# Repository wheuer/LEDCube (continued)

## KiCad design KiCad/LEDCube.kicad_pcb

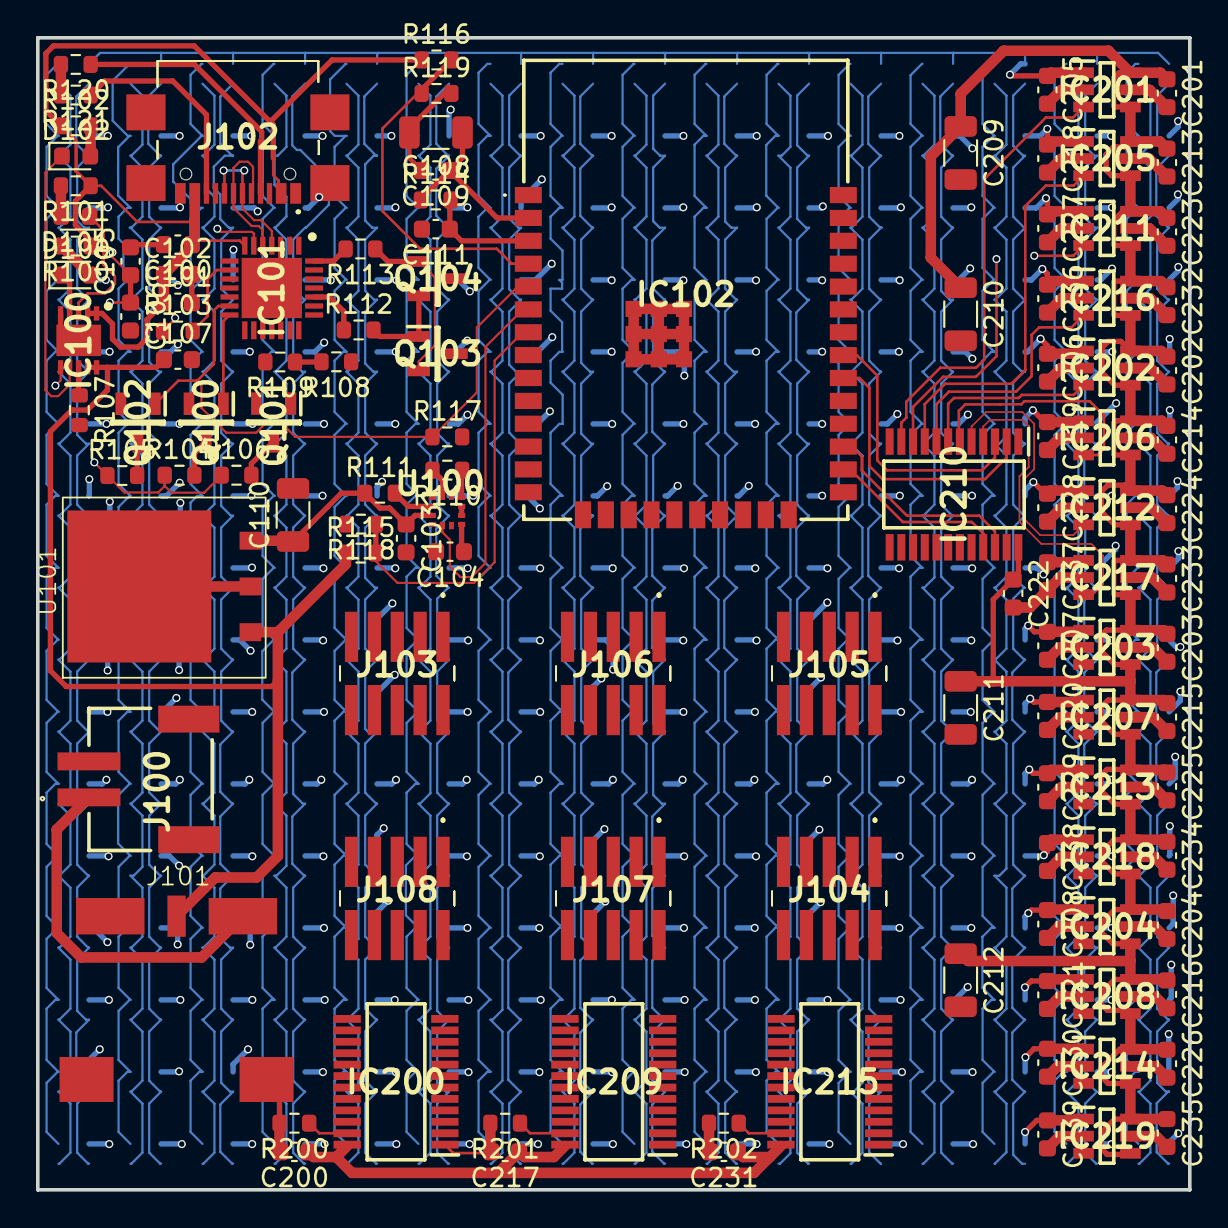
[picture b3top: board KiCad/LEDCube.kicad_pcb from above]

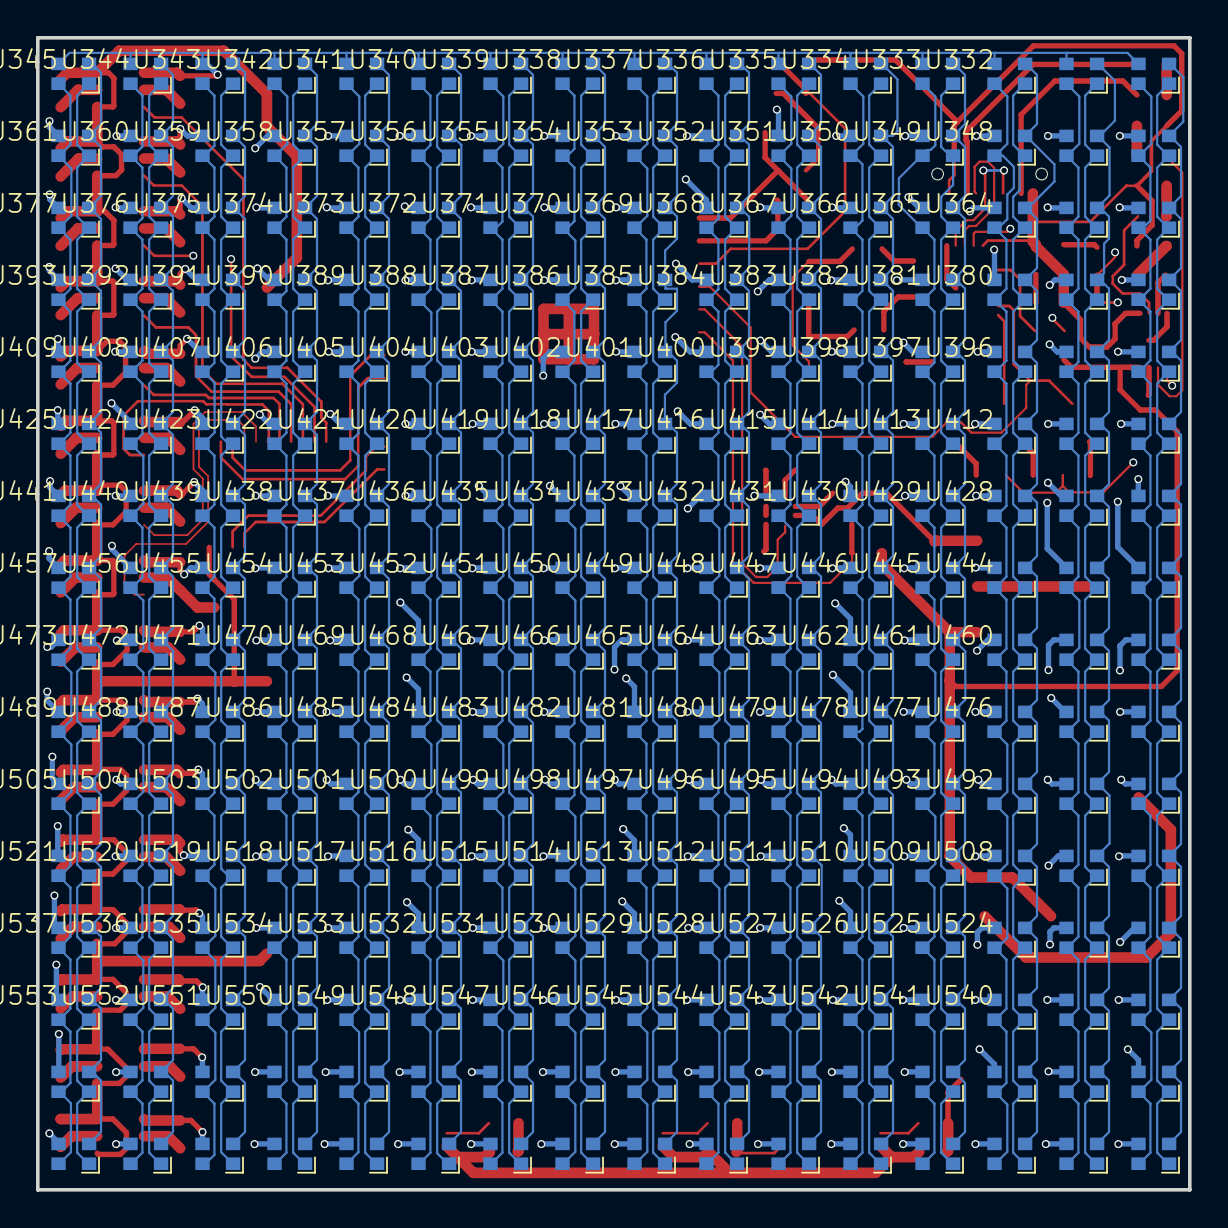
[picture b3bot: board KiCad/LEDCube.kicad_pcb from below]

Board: 4 copper layers, 64.0 x 64.0 mm, 375 parts (256 on the bottom side), 137 nets.

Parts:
C100, C102, C105, C107: 4.7u; C_0603_1608Metric
C101, C103, C104, C106, C109, C200, C205, C206, C207, C208, C217, C218, C219, C220, C221, C222, C227, C228, C229, C230, C231, C236, C237, C238, C239: 100n; C_0603_1608Metric
C108, C110, C209, C210, C211, C212: 47u; C_1206_3216Metric
C111, C201, C202, C203, C204, C213, C214, C215, C216, C223, C224, C225, C226, C232, C233, C234, C235: 1u; C_0603_1608Metric
D100: Green; LED_0603_1608Metric
D101: Amber; LED_0603_1608Metric
D102: Blue; LED_0603_1608Metric
IC100: MCP73833T-FCI_MF; SON50P300X300X100-11N-D
IC101: CP2102N-A02-GQFN28; QFN50P500X500X80-29N-D
IC102: ESP32-WROOM-32E-H4; ESP32WROOM32EH4
IC200, IC209, IC215: STP16CPC26PTR; SOP64P600X173-24N
IC201, IC202, IC203, IC204, IC205, IC206, IC207, IC208, IC211, IC212, IC213, IC214, IC216, IC217, IC218, IC219: AP2281-3WG-7; SOT95P285X140-6N
IC210: 74HC4514PW,118; SOP65P640X110-24N
J100: 1769
J101: PowerSwitch
J102: USB4110-GF-A; USB4110GFA
J103, J104, J105, J106, J107, J108: 15-91-0100; FTSH10501FDVK
Q100, Q101, Q102, Q103, Q104: Q_NMOS_GSD; SOT96P237X111-3N
R100, R101, R102, R103, R112, R113: 1k; R_0603_1608Metric
R104: 3.3k; R_0603_1608Metric
R105, R107, R110, R111, R114, R115, R116, R117, R118, R119: 10k; R_0603_1608Metric
R106: 2.49k; R_0603_1608Metric
R108: 22.1k; R_0603_1608Metric
R109: 47.5k; R_0603_1608Metric
R120, R121: 5.1k; R_0603_1608Metric
R200, R201, R202: 4.12k; R_0603_1608Metric
U100: BOSCH_LGA-12
U101: MIC37300-3.3-SPAK3
U300, U301, U302, U303, U304, U305, U306, U307, U308, U309, U310, U311, U312, U313, U314, U315, U316, U317, U318, U319, U320, U321, U322, U323, U324, U325, U326, U327, U328, U329, U330, U331, U332, U333, U334, U335, U336, U337, U338, U339, U340, U341, U342, U343, U344, U345, U346, U347, U348, U349, U350, U351, U352, U353, U354, U355, U356, U357, U358, U359, U360, U361, U362, U363, U364, U365, U366, U367, U368, U369, U370, U371, U372, U373, U374, U375, U376, U377, U378, U379, U380, U381, U382, U383, U384, U385, U386, U387, U388, U389, U390, U391, U392, U393, U394, U395, U396, U397, U398, U399, U400, U401, U402, U403, U404, U405, U406, U407, U408, U409, U410, U411, U412, U413, U414, U415, U416, U417, U418, U419, U420, U421, U422, U423, U424, U425, U426, U427, U428, U429, U430, U431, U432, U433, U434, U435, U436, U437, U438, U439, U440, U441, U442, U443, U444, U445, U446, U447, U448, U449, U450, U451, U452, U453, U454, U455, U456, U457, U458, U459, U460, U461, U462, U463, U464, U465, U466, U467, U468, U469, U470, U471, U472, U473, U474, U475, U476, U477, U478, U479, U480, U481, U482, U483, U484, U485, U486, U487, U488, U489, U490, U491, U492, U493, U494, U495, U496, U497, U498, U499, U500, U501, U502, U503, U504, U505, U506, U507, U508, U509, U510, U511, U512, U513, U514, U515, U516, U517, U518, U519, U520, U521, U522, U523, U524, U525, U526, U527, U528, U529, U530, U531, U532, U533, U534, U535, U536, U537, U538, U539, U540, U541, U542, U543, U544, U545, U546, U547, U548, U549, U550, U551, U552, U553, U554, U555: RGB_LED

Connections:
+3V3: C103.1, C104.1, C108.1, C109.1, C110.1, C200.1, C201.1, C202.1, C203.1, C204.1, C209.1, C210.1, C211.1, C212.1, C213.1, C214.1, C215.1, C216.1, C217.1, C222.1, C223.1, C224.1, C225.1, C226.1, C231.1, C232.1, C233.1, C234.1, C235.1, IC102.2 (3V3), IC200.24 (VDD), IC201.4 (IN_1), IC201.6 (IN_2), IC202.4 (IN_1), IC202.6 (IN_2), IC203.4 (IN_1), IC203.6 (IN_2), IC204.4 (IN_1), IC204.6 (IN_2), IC205.4 (IN_1), IC205.6 (IN_2), IC206.4 (IN_1), IC206.6 (IN_2), IC207.4 (IN_1), IC207.6 (IN_2), IC208.4 (IN_1), IC208.6 (IN_2), IC209.24 (VDD), IC210.24 (VCC), IC211.4 (IN_1), IC211.6 (IN_2), IC212.4 (IN_1), IC212.6 (IN_2), IC213.4 (IN_1), IC213.6 (IN_2), IC214.4 (IN_1), IC214.6 (IN_2), IC215.24 (VDD), IC216.4 (IN_1), IC216.6 (IN_2), IC217.4 (IN_1), IC217.6 (IN_2), IC218.4 (IN_1), IC218.6 (IN_2), IC219.4 (IN_1), IC219.6 (IN_2), J103.1, J104.1, J105.1, J106.1, J107.1, J108.1, R110.1, R111.1, R114.1, U100.3 (VDDIO), U100.7 (VDD), U100.10 (CSB), U101.3 (VOUT)
BMA400_INT1: IC102.6 (IO34), U100.5 (INT1)
BRIGHTNESS_PWM: IC102.28 (IO17), IC200.21 (~OE), IC209.21 (~OE), IC215.21 (~OE), J103.9, J104.9, J105.9, J106.9, J107.9, J108.9
CHG_1.5A: IC101.14 (CHR1), Q100.1 (G)
CHG_100mA: IC101.13 (CHREN), IC102.5 (SENSOR_VN), Q102.1 (G), R117.1
CHG_500mA: IC101.15 (CHR0), Q101.1 (G)
CP2102_VDD: C105.1, C106.1, IC101.6 (VDD), R103.1
D+: IC101.4 (D+), J102.A6 (A6/D+1), J102.B6 (B6/D+2)
D-: IC101.5 (D-), J102.A7 (A7/D-1), J102.B7 (B7/D-2)
DTR: IC101.28 (DTR), R113.2
GND: C100.2, C101.2, C102.2, C103.2, C104.2, C105.2, C106.2, C107.2, C108.2, C109.2, C110.2, C111.2, C200.2, C201.2, C202.2, C203.2, C204.2, C205.2, C206.2, C207.2, C208.2, C209.2, C210.2, C211.2, C212.2, C213.2, C214.2, C215.2, C216.2, C217.2, C218.2, C219.2, C220.2, C221.2, C222.2, C223.2, C224.2, C225.2, C226.2, C227.2, C228.2, C229.2, C230.2, C231.2, C232.2, C233.2, C234.2, C235.2, C236.2, C237.2, C238.2, C239.2, IC100.5 (VSS), IC100.11 (EP), IC101.3 (GND), IC101.29 (BGND), IC102.1 (GND_1), IC102.15 (GND_2), IC102.38 (GND_3), IC102.39 (GND_4), IC102.40 (GND_5), IC102.41 (GND_6), IC102.42 (GND_7), IC102.43 (GND_8), IC102.44 (GND_9), IC102.45 (GND_10), IC102.46 (GND_11), IC102.47 (GND_12), IC200.1 (GND), IC201.2 (GND_1), IC201.5 (GND_2), IC202.2 (GND_1), IC202.5 (GND_2), IC203.2 (GND_1), IC203.5 (GND_2), IC204.2 (GND_1), IC204.5 (GND_2), IC205.2 (GND_1), IC205.5 (GND_2), IC206.2 (GND_1), IC206.5 (GND_2), IC207.2 (GND_1), IC207.5 (GND_2), IC208.2 (GND_1), IC208.5 (GND_2), IC209.1 (GND), IC210.12 (GND), IC210.23 (~E), IC211.2 (GND_1), IC211.5 (GND_2), IC212.2 (GND_1), IC212.5 (GND_2), IC213.2 (GND_1), IC213.5 (GND_2), IC214.2 (GND_1), IC214.5 (GND_2), IC215.1 (GND), IC216.2 (GND_1), IC216.5 (GND_2), IC217.2 (GND_1), IC217.5 (GND_2), IC218.2 (GND_1), IC218.5 (GND_2), IC219.2 (GND_1), IC219.5 (GND_2), J100.2 (-), J101.1 (POS1), J101.4 (CASE), J102.A1 (A1/GND), J102.A12 (A12/GND), J102.B1 (B1/GND), J102.B12 (B12/GND), J103.10, J104.10, J105.10, J106.10, J107.10, J108.10, Q100.2 (S), Q101.2 (S), Q102.2 (S), R107.2, R109.2, R117.2, R118.2, R119.2, R120.2, R121.2, R200.2, R201.2, R202.2, U100.1 (SDO), U100.8 (GNDIO), U100.9 (GND), U101.2 (GND)
IO0: IC102.25 (IO0), Q103.3 (D)
LATCH: IC102.33 (IO21), IC200.4 (LE), IC209.4 (LE), IC210.1 (LE), IC215.4 (LE), J103.5, J104.5, J105.5, J106.5, J107.5, J108.5
LED_0_BLUE: IC200.7 (OUT2), U300.2 (Blue), U316.2 (Blue), U332.2 (Blue), U348.2 (Blue), U364.2 (Blue), U380.2 (Blue), U396.2 (Blue), U412.2 (Blue), U428.2 (Blue), U444.2 (Blue), U460.2 (Blue), U476.2 (Blue), U492.2 (Blue), U508.2 (Blue), U524.2 (Blue), U540.2 (Blue)
LED_0_GREEN: IC200.6 (OUT1), U300.4 (Green), U316.4 (Green), U332.4 (Green), U348.4 (Green), U364.4 (Green), U380.4 (Green), U396.4 (Green), U412.4 (Green), U428.4 (Green), U444.4 (Green), U460.4 (Green), U476.4 (Green), U492.4 (Green), U508.4 (Green), U524.4 (Green), U540.4 (Green)
LED_0_RED: IC200.5 (OUT0), U300.1 (Red), U316.1 (Red), U332.1 (Red), U348.1 (Red), U364.1 (Red), U380.1 (Red), U396.1 (Red), U412.1 (Red), U428.1 (Red), U444.1 (Red), U460.1 (Red), U476.1 (Red), U492.1 (Red), U508.1 (Red), U524.1 (Red), U540.1 (Red)
LED_1_BLUE: IC200.10 (OUT5), U301.2 (Blue), U317.2 (Blue), U333.2 (Blue), U349.2 (Blue), U365.2 (Blue), U381.2 (Blue), U397.2 (Blue), U413.2 (Blue), U429.2 (Blue), U445.2 (Blue), U461.2 (Blue), U477.2 (Blue), U493.2 (Blue), U509.2 (Blue), U525.2 (Blue), U541.2 (Blue)
LED_1_GREEN: IC200.9 (OUT4), U301.4 (Green), U317.4 (Green), U333.4 (Green), U349.4 (Green), U365.4 (Green), U381.4 (Green), U397.4 (Green), U413.4 (Green), U429.4 (Green), U445.4 (Green), U461.4 (Green), U477.4 (Green), U493.4 (Green), U509.4 (Green), U525.4 (Green), U541.4 (Green)
LED_1_RED: IC200.8 (OUT3), U301.1 (Red), U317.1 (Red), U333.1 (Red), U349.1 (Red), U365.1 (Red), U381.1 (Red), U397.1 (Red), U413.1 (Red), U429.1 (Red), U445.1 (Red), U461.1 (Red), U477.1 (Red), U493.1 (Red), U509.1 (Red), U525.1 (Red), U541.1 (Red)
LED_2_BLUE: IC200.13 (OUT8), U302.2 (Blue), U318.2 (Blue), U334.2 (Blue), U350.2 (Blue), U366.2 (Blue), U382.2 (Blue), U398.2 (Blue), U414.2 (Blue), U430.2 (Blue), U446.2 (Blue), U462.2 (Blue), U478.2 (Blue), U494.2 (Blue), U510.2 (Blue), U526.2 (Blue), U542.2 (Blue)
LED_2_GREEN: IC200.12 (OUT7), U302.4 (Green), U318.4 (Green), U334.4 (Green), U350.4 (Green), U366.4 (Green), U382.4 (Green), U398.4 (Green), U414.4 (Green), U430.4 (Green), U446.4 (Green), U462.4 (Green), U478.4 (Green), U494.4 (Green), U510.4 (Green), U526.4 (Green), U542.4 (Green)
LED_2_RED: IC200.11 (OUT6), U302.1 (Red), U318.1 (Red), U334.1 (Red), U350.1 (Red), U366.1 (Red), U382.1 (Red), U398.1 (Red), U414.1 (Red), U430.1 (Red), U446.1 (Red), U462.1 (Red), U478.1 (Red), U494.1 (Red), U510.1 (Red), U526.1 (Red), U542.1 (Red)
LED_3_BLUE: IC200.16 (OUT11), U303.2 (Blue), U319.2 (Blue), U335.2 (Blue), U351.2 (Blue), U367.2 (Blue), U383.2 (Blue), U399.2 (Blue), U415.2 (Blue), U431.2 (Blue), U447.2 (Blue), U463.2 (Blue), U479.2 (Blue), U495.2 (Blue), U511.2 (Blue), U527.2 (Blue), U543.2 (Blue)
LED_3_GREEN: IC200.15 (OUT10), U303.4 (Green), U319.4 (Green), U335.4 (Green), U351.4 (Green), U367.4 (Green), U383.4 (Green), U399.4 (Green), U415.4 (Green), U431.4 (Green), U447.4 (Green), U463.4 (Green), U479.4 (Green), U495.4 (Green), U511.4 (Green), U527.4 (Green), U543.4 (Green)
LED_3_RED: IC200.14 (OUT9), U303.1 (Red), U319.1 (Red), U335.1 (Red), U351.1 (Red), U367.1 (Red), U383.1 (Red), U399.1 (Red), U415.1 (Red), U431.1 (Red), U447.1 (Red), U463.1 (Red), U479.1 (Red), U495.1 (Red), U511.1 (Red), U527.1 (Red), U543.1 (Red)
LED_4_BLUE: IC200.19 (OUT14), U304.2 (Blue), U320.2 (Blue), U336.2 (Blue), U352.2 (Blue), U368.2 (Blue), U384.2 (Blue), U400.2 (Blue), U416.2 (Blue), U432.2 (Blue), U448.2 (Blue), U464.2 (Blue), U480.2 (Blue), U496.2 (Blue), U512.2 (Blue), U528.2 (Blue), U544.2 (Blue)
LED_4_GREEN: IC200.18 (OUT13), U304.4 (Green), U320.4 (Green), U336.4 (Green), U352.4 (Green), U368.4 (Green), U384.4 (Green), U400.4 (Green), U416.4 (Green), U432.4 (Green), U448.4 (Green), U464.4 (Green), U480.4 (Green), U496.4 (Green), U512.4 (Green), U528.4 (Green), U544.4 (Green)
LED_4_RED: IC200.17 (OUT12), U304.1 (Red), U320.1 (Red), U336.1 (Red), U352.1 (Red), U368.1 (Red), U384.1 (Red), U400.1 (Red), U416.1 (Red), U432.1 (Red), U448.1 (Red), U464.1 (Red), U480.1 (Red), U496.1 (Red), U512.1 (Red), U528.1 (Red), U544.1 (Red)
LED_5_BLUE: IC209.6 (OUT1), U305.2 (Blue), U321.2 (Blue), U337.2 (Blue), U353.2 (Blue), U369.2 (Blue), U385.2 (Blue), U401.2 (Blue), U417.2 (Blue), U433.2 (Blue), U449.2 (Blue), U465.2 (Blue), U481.2 (Blue), U497.2 (Blue), U513.2 (Blue), U529.2 (Blue), U545.2 (Blue)
LED_5_GREEN: IC209.5 (OUT0), U305.4 (Green), U321.4 (Green), U337.4 (Green), U353.4 (Green), U369.4 (Green), U385.4 (Green), U401.4 (Green), U417.4 (Green), U433.4 (Green), U449.4 (Green), U465.4 (Green), U481.4 (Green), U497.4 (Green), U513.4 (Green), U529.4 (Green), U545.4 (Green)
LED_5_RED: IC200.20 (OUT15), U305.1 (Red), U321.1 (Red), U337.1 (Red), U353.1 (Red), U369.1 (Red), U385.1 (Red), U401.1 (Red), U417.1 (Red), U433.1 (Red), U449.1 (Red), U465.1 (Red), U481.1 (Red), U497.1 (Red), U513.1 (Red), U529.1 (Red), U545.1 (Red)
LED_6_BLUE: IC209.9 (OUT4), U306.2 (Blue), U322.2 (Blue), U338.2 (Blue), U354.2 (Blue), U370.2 (Blue), U386.2 (Blue), U402.2 (Blue), U418.2 (Blue), U434.2 (Blue), U450.2 (Blue), U466.2 (Blue), U482.2 (Blue), U498.2 (Blue), U514.2 (Blue), U530.2 (Blue), U546.2 (Blue)
LED_6_GREEN: IC209.8 (OUT3), U306.4 (Green), U322.4 (Green), U338.4 (Green), U354.4 (Green), U370.4 (Green), U386.4 (Green), U402.4 (Green), U418.4 (Green), U434.4 (Green), U450.4 (Green), U466.4 (Green), U482.4 (Green), U498.4 (Green), U514.4 (Green), U530.4 (Green), U546.4 (Green)
LED_6_RED: IC209.7 (OUT2), U306.1 (Red), U322.1 (Red), U338.1 (Red), U354.1 (Red), U370.1 (Red), U386.1 (Red), U402.1 (Red), U418.1 (Red), U434.1 (Red), U450.1 (Red), U466.1 (Red), U482.1 (Red), U498.1 (Red), U514.1 (Red), U530.1 (Red), U546.1 (Red)
LED_7_BLUE: IC209.12 (OUT7), U307.2 (Blue), U323.2 (Blue), U339.2 (Blue), U355.2 (Blue), U371.2 (Blue), U387.2 (Blue), U403.2 (Blue), U419.2 (Blue), U435.2 (Blue), U451.2 (Blue), U467.2 (Blue), U483.2 (Blue), U499.2 (Blue), U515.2 (Blue), U531.2 (Blue), U547.2 (Blue)
LED_7_GREEN: IC209.11 (OUT6), U307.4 (Green), U323.4 (Green), U339.4 (Green), U355.4 (Green), U371.4 (Green), U387.4 (Green), U403.4 (Green), U419.4 (Green), U435.4 (Green), U451.4 (Green), U467.4 (Green), U483.4 (Green), U499.4 (Green), U515.4 (Green), U531.4 (Green), U547.4 (Green)
LED_7_RED: IC209.10 (OUT5), U307.1 (Red), U323.1 (Red), U339.1 (Red), U355.1 (Red), U371.1 (Red), U387.1 (Red), U403.1 (Red), U419.1 (Red), U435.1 (Red), U451.1 (Red), U467.1 (Red), U483.1 (Red), U499.1 (Red), U515.1 (Red), U531.1 (Red), U547.1 (Red)
LED_8_BLUE: IC209.15 (OUT10), U308.2 (Blue), U324.2 (Blue), U340.2 (Blue), U356.2 (Blue), U372.2 (Blue), U388.2 (Blue), U404.2 (Blue), U420.2 (Blue), U436.2 (Blue), U452.2 (Blue), U468.2 (Blue), U484.2 (Blue), U500.2 (Blue), U516.2 (Blue), U532.2 (Blue), U548.2 (Blue)
LED_8_GREEN: IC209.14 (OUT9), U308.4 (Green), U324.4 (Green), U340.4 (Green), U356.4 (Green), U372.4 (Green), U388.4 (Green), U404.4 (Green), U420.4 (Green), U436.4 (Green), U452.4 (Green), U468.4 (Green), U484.4 (Green), U500.4 (Green), U516.4 (Green), U532.4 (Green), U548.4 (Green)
LED_8_RED: IC209.13 (OUT8), U308.1 (Red), U324.1 (Red), U340.1 (Red), U356.1 (Red), U372.1 (Red), U388.1 (Red), U404.1 (Red), U420.1 (Red), U436.1 (Red), U452.1 (Red), U468.1 (Red), U484.1 (Red), U500.1 (Red), U516.1 (Red), U532.1 (Red), U548.1 (Red)
LED_9_BLUE: IC209.18 (OUT13), U309.2 (Blue), U325.2 (Blue), U341.2 (Blue), U357.2 (Blue), U373.2 (Blue), U389.2 (Blue), U405.2 (Blue), U421.2 (Blue), U437.2 (Blue), U453.2 (Blue), U469.2 (Blue), U485.2 (Blue), U501.2 (Blue), U517.2 (Blue), U533.2 (Blue), U549.2 (Blue)
LED_9_GREEN: IC209.17 (OUT12), U309.4 (Green), U325.4 (Green), U341.4 (Green), U357.4 (Green), U373.4 (Green), U389.4 (Green), U405.4 (Green), U421.4 (Green), U437.4 (Green), U453.4 (Green), U469.4 (Green), U485.4 (Green), U501.4 (Green), U517.4 (Green), U533.4 (Green), U549.4 (Green)
LED_9_RED: IC209.16 (OUT11), U309.1 (Red), U325.1 (Red), U341.1 (Red), U357.1 (Red), U373.1 (Red), U389.1 (Red), U405.1 (Red), U421.1 (Red), U437.1 (Red), U453.1 (Red), U469.1 (Red), U485.1 (Red), U501.1 (Red), U517.1 (Red), U533.1 (Red), U549.1 (Red)
LED_10_BLUE: IC215.5 (OUT0), U310.2 (Blue), U326.2 (Blue), U342.2 (Blue), U358.2 (Blue), U374.2 (Blue), U390.2 (Blue), U406.2 (Blue), U422.2 (Blue), U438.2 (Blue), U454.2 (Blue), U470.2 (Blue), U486.2 (Blue), U502.2 (Blue), U518.2 (Blue), U534.2 (Blue), U550.2 (Blue)
LED_10_GREEN: IC209.20 (OUT15), U310.4 (Green), U326.4 (Green), U342.4 (Green), U358.4 (Green), U374.4 (Green), U390.4 (Green), U406.4 (Green), U422.4 (Green), U438.4 (Green), U454.4 (Green), U470.4 (Green), U486.4 (Green), U502.4 (Green), U518.4 (Green), U534.4 (Green), U550.4 (Green)
LED_10_RED: IC209.19 (OUT14), U310.1 (Red), U326.1 (Red), U342.1 (Red), U358.1 (Red), U374.1 (Red), U390.1 (Red), U406.1 (Red), U422.1 (Red), U438.1 (Red), U454.1 (Red), U470.1 (Red), U486.1 (Red), U502.1 (Red), U518.1 (Red), U534.1 (Red), U550.1 (Red)
LED_11_BLUE: IC215.8 (OUT3), U311.2 (Blue), U327.2 (Blue), U343.2 (Blue), U359.2 (Blue), U375.2 (Blue), U391.2 (Blue), U407.2 (Blue), U423.2 (Blue), U439.2 (Blue), U455.2 (Blue), U471.2 (Blue), U487.2 (Blue), U503.2 (Blue), U519.2 (Blue), U535.2 (Blue), U551.2 (Blue)
LED_11_GREEN: IC215.7 (OUT2), U311.4 (Green), U327.4 (Green), U343.4 (Green), U359.4 (Green), U375.4 (Green), U391.4 (Green), U407.4 (Green), U423.4 (Green), U439.4 (Green), U455.4 (Green), U471.4 (Green), U487.4 (Green), U503.4 (Green), U519.4 (Green), U535.4 (Green), U551.4 (Green)
LED_11_RED: IC215.6 (OUT1), U311.1 (Red), U327.1 (Red), U343.1 (Red), U359.1 (Red), U375.1 (Red), U391.1 (Red), U407.1 (Red), U423.1 (Red), U439.1 (Red), U455.1 (Red), U471.1 (Red), U487.1 (Red), U503.1 (Red), U519.1 (Red), U535.1 (Red), U551.1 (Red)
LED_12_BLUE: IC215.11 (OUT6), U312.2 (Blue), U328.2 (Blue), U344.2 (Blue), U360.2 (Blue), U376.2 (Blue), U392.2 (Blue), U408.2 (Blue), U424.2 (Blue), U440.2 (Blue), U456.2 (Blue), U472.2 (Blue), U488.2 (Blue), U504.2 (Blue), U520.2 (Blue), U536.2 (Blue), U552.2 (Blue)
LED_12_GREEN: IC215.10 (OUT5), U312.4 (Green), U328.4 (Green), U344.4 (Green), U360.4 (Green), U376.4 (Green), U392.4 (Green), U408.4 (Green), U424.4 (Green), U440.4 (Green), U456.4 (Green), U472.4 (Green), U488.4 (Green), U504.4 (Green), U520.4 (Green), U536.4 (Green), U552.4 (Green)
LED_12_RED: IC215.9 (OUT4), U312.1 (Red), U328.1 (Red), U344.1 (Red), U360.1 (Red), U376.1 (Red), U392.1 (Red), U408.1 (Red), U424.1 (Red), U440.1 (Red), U456.1 (Red), U472.1 (Red), U488.1 (Red), U504.1 (Red), U520.1 (Red), U536.1 (Red), U552.1 (Red)
LED_13_BLUE: IC215.14 (OUT9), U313.2 (Blue), U329.2 (Blue), U345.2 (Blue), U361.2 (Blue), U377.2 (Blue), U393.2 (Blue), U409.2 (Blue), U425.2 (Blue), U441.2 (Blue), U457.2 (Blue), U473.2 (Blue), U489.2 (Blue), U505.2 (Blue), U521.2 (Blue), U537.2 (Blue), U553.2 (Blue)
LED_13_GREEN: IC215.13 (OUT8), U313.4 (Green), U329.4 (Green), U345.4 (Green), U361.4 (Green), U377.4 (Green), U393.4 (Green), U409.4 (Green), U425.4 (Green), U441.4 (Green), U457.4 (Green), U473.4 (Green), U489.4 (Green), U505.4 (Green), U521.4 (Green), U537.4 (Green), U553.4 (Green)
LED_13_RED: IC215.12 (OUT7), U313.1 (Red), U329.1 (Red), U345.1 (Red), U361.1 (Red), U377.1 (Red), U393.1 (Red), U409.1 (Red), U425.1 (Red), U441.1 (Red), U457.1 (Red), U473.1 (Red), U489.1 (Red), U505.1 (Red), U521.1 (Red), U537.1 (Red), U553.1 (Red)
LED_14_BLUE: IC215.17 (OUT12), U314.2 (Blue), U330.2 (Blue), U346.2 (Blue), U362.2 (Blue), U378.2 (Blue), U394.2 (Blue), U410.2 (Blue), U426.2 (Blue), U442.2 (Blue), U458.2 (Blue), U474.2 (Blue), U490.2 (Blue), U506.2 (Blue), U522.2 (Blue), U538.2 (Blue), U554.2 (Blue)
LED_14_GREEN: IC215.16 (OUT11), U314.4 (Green), U330.4 (Green), U346.4 (Green), U362.4 (Green), U378.4 (Green), U394.4 (Green), U410.4 (Green), U426.4 (Green), U442.4 (Green), U458.4 (Green), U474.4 (Green), U490.4 (Green), U506.4 (Green), U522.4 (Green), U538.4 (Green), U554.4 (Green)
LED_14_RED: IC215.15 (OUT10), U314.1 (Red), U330.1 (Red), U346.1 (Red), U362.1 (Red), U378.1 (Red), U394.1 (Red), U410.1 (Red), U426.1 (Red), U442.1 (Red), U458.1 (Red), U474.1 (Red), U490.1 (Red), U506.1 (Red), U522.1 (Red), U538.1 (Red), U554.1 (Red)
LED_15_BLUE: IC215.20 (OUT15), U315.2 (Blue), U331.2 (Blue), U347.2 (Blue), U363.2 (Blue), U379.2 (Blue), U395.2 (Blue), U411.2 (Blue), U427.2 (Blue), U443.2 (Blue), U459.2 (Blue), U475.2 (Blue), U491.2 (Blue), U507.2 (Blue), U523.2 (Blue), U539.2 (Blue), U555.2 (Blue)
LED_15_GREEN: IC215.19 (OUT14), U315.4 (Green), U331.4 (Green), U347.4 (Green), U363.4 (Green), U379.4 (Green), U395.4 (Green), U411.4 (Green), U427.4 (Green), U443.4 (Green), U459.4 (Green), U475.4 (Green), U491.4 (Green), U507.4 (Green), U523.4 (Green), U539.4 (Green), U555.4 (Green)
LED_15_RED: IC215.18 (OUT13), U315.1 (Red), U331.1 (Red), U347.1 (Red), U363.1 (Red), U379.1 (Red), U395.1 (Red), U411.1 (Red), U427.1 (Red), U443.1 (Red), U459.1 (Red), U475.1 (Red), U491.1 (Red), U507.1 (Red), U523.1 (Red), U539.1 (Red), U555.1 (Red)
MASTER_CLK: IC102.36 (IO22), IC200.3 (CLK), IC209.3 (CLK), IC215.3 (CLK), J103.7, J104.7, J105.7, J106.7, J107.7, J108.7
MUX_B0: IC102.30 (IO18), IC210.2 (A0), J103.8, J104.8, J105.8, J106.8, J107.8, J108.8
MUX_B1: IC102.31 (IO19), IC210.3 (A1), J103.6, J104.6, J105.6, J106.6, J107.6, J108.6
MUX_B2: IC102.26 (IO4), IC210.21 (A2), J103.4, J104.4, J105.4, J106.4, J107.4, J108.4
MUX_B3: IC102.27 (IO16), IC210.22 (A3), J103.2, J104.2, J105.2, J106.2, J107.2, J108.2
unnamed: D100.2 (A), R100.2
unnamed: D100.1 (K), IC100.4 (STAT2)
unnamed: D101.2 (A), R101.2
unnamed: D101.1 (K), IC100.3 (STAT1)
unnamed: D102.2 (A), R102.2
unnamed: D102.1 (K), IC100.7 (~PG)
unnamed: IC100.6 (PROG), R104.1, R105.1, R106.1
unnamed: IC100.8 (THERM), R107.1
unnamed: IC101.9 (RSTB), R103.2
unnamed: IC101.8 (VBUS), R108.2, R109.1
unnamed: C111.1, IC102.3 (EN), R114.2
unnamed: IC200.23 (R-EXT), R200.1
unnamed: IC200.22 (SDO), IC209.2 (SDI)
unnamed: IC209.23 (R-EXT), R201.1
unnamed: IC209.22 (SDO), IC215.2 (SDI)
unnamed: IC215.23 (R-EXT), R202.1
unnamed: J100.1 (+), J101.3 (POS2)
unnamed: J102.A5 (A5/CC1), R120.1
unnamed: J102.B5 (B5/CC2), R121.1
unnamed: Q100.3 (D), R104.2
unnamed: Q101.3 (D), R106.2
unnamed: Q102.3 (D), R105.2
unnamed: Q103.1 (G), Q104.2 (S), R112.2
unnamed: Q103.2 (S), Q104.1 (G), R113.1
ROW_0_EN: IC201.3 (EN), IC210.11 (Q0)
ROW_0_OUT: C205.1, IC201.1 (OUT), U300.3 (VCC), U301.3 (VCC), U302.3 (VCC), U303.3 (VCC), U304.3 (VCC), U305.3 (VCC), U306.3 (VCC), U307.3 (VCC), U308.3 (VCC), U309.3 (VCC), U310.3 (VCC), U311.3 (VCC), U312.3 (VCC), U313.3 (VCC), U314.3 (VCC), U315.3 (VCC)
ROW_1_EN: IC205.3 (EN), IC210.9 (Q1)
ROW_1_OUT: C218.1, IC205.1 (OUT), U316.3 (VCC), U317.3 (VCC), U318.3 (VCC), U319.3 (VCC), U320.3 (VCC), U321.3 (VCC), U322.3 (VCC), U323.3 (VCC), U324.3 (VCC), U325.3 (VCC), U326.3 (VCC), U327.3 (VCC), U328.3 (VCC), U329.3 (VCC), U330.3 (VCC), U331.3 (VCC)
ROW_2_EN: IC210.10 (Q2), IC211.3 (EN)
ROW_2_OUT: C227.1, IC211.1 (OUT), U332.3 (VCC), U333.3 (VCC), U334.3 (VCC), U335.3 (VCC), U336.3 (VCC), U337.3 (VCC), U338.3 (VCC), U339.3 (VCC), U340.3 (VCC), U341.3 (VCC), U342.3 (VCC), U343.3 (VCC), U344.3 (VCC), U345.3 (VCC), U346.3 (VCC), U347.3 (VCC)
ROW_3_EN: IC210.8 (Q3), IC216.3 (EN)
ROW_3_OUT: C236.1, IC216.1 (OUT), U348.3 (VCC), U349.3 (VCC), U350.3 (VCC), U351.3 (VCC), U352.3 (VCC), U353.3 (VCC), U354.3 (VCC), U355.3 (VCC), U356.3 (VCC), U357.3 (VCC), U358.3 (VCC), U359.3 (VCC), U360.3 (VCC), U361.3 (VCC), U362.3 (VCC), U363.3 (VCC)
ROW_4_EN: IC202.3 (EN), IC210.7 (Q4)
ROW_4_OUT: C206.1, IC202.1 (OUT), U364.3 (VCC), U365.3 (VCC), U366.3 (VCC), U367.3 (VCC), U368.3 (VCC), U369.3 (VCC), U370.3 (VCC), U371.3 (VCC), U372.3 (VCC), U373.3 (VCC), U374.3 (VCC), U375.3 (VCC), U376.3 (VCC), U377.3 (VCC), U378.3 (VCC), U379.3 (VCC)
ROW_5_EN: IC206.3 (EN), IC210.6 (Q5)
ROW_5_OUT: C219.1, IC206.1 (OUT), U380.3 (VCC), U381.3 (VCC), U382.3 (VCC), U383.3 (VCC), U384.3 (VCC), U385.3 (VCC), U386.3 (VCC), U387.3 (VCC), U388.3 (VCC), U389.3 (VCC), U390.3 (VCC), U391.3 (VCC), U392.3 (VCC), U393.3 (VCC), U394.3 (VCC), U395.3 (VCC)
ROW_6_EN: IC210.5 (Q6), IC212.3 (EN)
ROW_6_OUT: C228.1, IC212.1 (OUT), U396.3 (VCC), U397.3 (VCC), U398.3 (VCC), U399.3 (VCC), U400.3 (VCC), U401.3 (VCC), U402.3 (VCC), U403.3 (VCC), U404.3 (VCC), U405.3 (VCC), U406.3 (VCC), U407.3 (VCC), U408.3 (VCC), U409.3 (VCC), U410.3 (VCC), U411.3 (VCC)
ROW_7_EN: IC210.4 (Q7), IC217.3 (EN)
ROW_7_OUT: C237.1, IC217.1 (OUT), U412.3 (VCC), U413.3 (VCC), U414.3 (VCC), U415.3 (VCC), U416.3 (VCC), U417.3 (VCC), U418.3 (VCC), U419.3 (VCC), U420.3 (VCC), U421.3 (VCC), U422.3 (VCC), U423.3 (VCC), U424.3 (VCC), U425.3 (VCC), U426.3 (VCC), U427.3 (VCC)
ROW_8_EN: IC203.3 (EN), IC210.18 (Q8)
ROW_8_OUT: C207.1, IC203.1 (OUT), U428.3 (VCC), U429.3 (VCC), U430.3 (VCC), U431.3 (VCC), U432.3 (VCC), U433.3 (VCC), U434.3 (VCC), U435.3 (VCC), U436.3 (VCC), U437.3 (VCC), U438.3 (VCC), U439.3 (VCC), U440.3 (VCC), U441.3 (VCC), U442.3 (VCC), U443.3 (VCC)
ROW_9_EN: IC207.3 (EN), IC210.17 (Q9)
ROW_9_OUT: C220.1, IC207.1 (OUT), U444.3 (VCC), U445.3 (VCC), U446.3 (VCC), U447.3 (VCC), U448.3 (VCC), U449.3 (VCC), U450.3 (VCC), U451.3 (VCC), U452.3 (VCC), U453.3 (VCC), U454.3 (VCC), U455.3 (VCC), U456.3 (VCC), U457.3 (VCC), U458.3 (VCC), U459.3 (VCC)
ROW_10_EN: IC210.20 (Q10), IC213.3 (EN)
ROW_10_OUT: C229.1, IC213.1 (OUT), U460.3 (VCC), U461.3 (VCC), U462.3 (VCC), U463.3 (VCC), U464.3 (VCC), U465.3 (VCC), U466.3 (VCC), U467.3 (VCC), U468.3 (VCC), U469.3 (VCC), U470.3 (VCC), U471.3 (VCC), U472.3 (VCC), U473.3 (VCC), U474.3 (VCC), U475.3 (VCC)
ROW_11_EN: IC210.19 (Q11), IC218.3 (EN)
ROW_11_OUT: C238.1, IC218.1 (OUT), U476.3 (VCC), U477.3 (VCC), U478.3 (VCC), U479.3 (VCC), U480.3 (VCC), U481.3 (VCC), U482.3 (VCC), U483.3 (VCC), U484.3 (VCC), U485.3 (VCC), U486.3 (VCC), U487.3 (VCC), U488.3 (VCC), U489.3 (VCC), U490.3 (VCC), U491.3 (VCC)
ROW_12_EN: IC204.3 (EN), IC210.14 (Q12)
ROW_12_OUT: C208.1, IC204.1 (OUT), U492.3 (VCC), U493.3 (VCC), U494.3 (VCC), U495.3 (VCC), U496.3 (VCC), U497.3 (VCC), U498.3 (VCC), U499.3 (VCC), U500.3 (VCC), U501.3 (VCC), U502.3 (VCC), U503.3 (VCC), U504.3 (VCC), U505.3 (VCC), U506.3 (VCC), U507.3 (VCC)
ROW_13_EN: IC208.3 (EN), IC210.13 (Q13)
ROW_13_OUT: C221.1, IC208.1 (OUT), U508.3 (VCC), U509.3 (VCC), U510.3 (VCC), U511.3 (VCC), U512.3 (VCC), U513.3 (VCC), U514.3 (VCC), U515.3 (VCC), U516.3 (VCC), U517.3 (VCC), U518.3 (VCC), U519.3 (VCC), U520.3 (VCC), U521.3 (VCC), U522.3 (VCC), U523.3 (VCC)
ROW_14_EN: IC210.16 (Q14), IC214.3 (EN)
ROW_14_OUT: C230.1, IC214.1 (OUT), U524.3 (VCC), U525.3 (VCC), U526.3 (VCC), U527.3 (VCC), U528.3 (VCC), U529.3 (VCC), U530.3 (VCC), U531.3 (VCC), U532.3 (VCC), U533.3 (VCC), U534.3 (VCC), U535.3 (VCC), U536.3 (VCC), U537.3 (VCC), U538.3 (VCC), U539.3 (VCC)
ROW_15_EN: IC210.15 (Q15), IC219.3 (EN)
ROW_15_OUT: C239.1, IC219.1 (OUT), U540.3 (VCC), U541.3 (VCC), U542.3 (VCC), U543.3 (VCC), U544.3 (VCC), U545.3 (VCC), U546.3 (VCC), U547.3 (VCC), U548.3 (VCC), U549.3 (VCC), U550.3 (VCC), U551.3 (VCC), U552.3 (VCC), U553.3 (VCC), U554.3 (VCC), U555.3 (VCC)
RTS: IC101.24 (RTS), R112.1
RXD: IC101.25 (RXD), IC102.35 (TXD0)
SCL: IC102.9 (IO33), R110.2, U100.12 (SCX)
SDA: IC102.8 (IO32), R111.2, U100.2 (SDX)
SERIAL_IN0: IC102.37 (IO23), IC200.2 (SDI), J103.3
SERIAL_IN1: IC102.10 (IO25), J106.3
SERIAL_IN2: IC102.11 (IO26), J105.3
SERIAL_IN3: IC102.12 (IO27), J108.3
SERIAL_IN4: IC102.13 (IO14), J104.3
SERIAL_IN5: IC102.16 (IO13), J107.3
TXD: IC101.26 (TXD), IC102.34 (RXD0)
VBAT: C107.1, IC100.9 (VBAT_1), IC100.10 (VBAT_2), J101.2 (Common), R115.1, U101.1 (VIN)
VBAT_SENSE: IC102.7 (IO35), R115.2, R118.1
VBUS: C100.1, C101.1, C102.1, IC100.1 (VDD_1), IC100.2 (VDD_2), IC101.7 (VREGIN), J102.A4 (A4/VBUS), J102.A9 (A9/VBUS), J102.B4 (B4/VBUS), J102.B9 (B9/VBUS), R100.1, R101.1, R102.1, R108.1, R116.1
VBUS_SENSE: IC102.4 (SENSOR_VP), R116.2, R119.1

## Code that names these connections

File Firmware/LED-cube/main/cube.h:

#ifndef __CUBE_H
#define __CUBE_H

#include <stdint.h>

#ifdef __cplusplus
extern "C" {
#endif

#define LATCH_PIN 18        // LED Driver latch common for every panel
#define BRIGHTNESS_PIN 23   // LED Driver EN pin common for every panel 
#define MASTER_CLK_PIN 21   // LED Driver CLK pin common for every panel
#define MUX_B0_PIN 22       // Bit 0 of row multiplexers, common for every panel
#define MUX_B1_PIN 19       // Bit 1 of row multiplexers, common for every panel
#define MUX_B2_PIN 4        // Bit 2 of row multiplexers, common for every panel
#define MUX_B3_PIN 17       // Bit 3 of row multiplexers, common for every panel

#define SERIAL_0_PIN 16
#define SERIAL_1_PIN 25
#define SERIAL_2_PIN 26
#define SERIAL_3_PIN 27
#define SERIAL_4_PIN 14
#define SERIAL_5_PIN 13

#define SERIAL_0_PIN_MASK (1 << SERIAL_0_PIN)
#define SERIAL_1_PIN_MASK (1 << SERIAL_1_PIN)
#define SERIAL_2_PIN_MASK (1 << SERIAL_2_PIN)
#define SERIAL_3_PIN_MASK (1 << SERIAL_3_PIN)
#define SERIAL_4_PIN_MASK (1 << SERIAL_4_PIN)
#define SERIAL_5_PIN_MASK (1 << SERIAL_5_PIN)

#define NUM_ROWS 16
#define NUM_COLUMNS 16
#define NUM_PANELS 6

// typedef struct
// {
//     union {
//         uint8_t r;
//         uint8_t red;
//     };
//     union {
//         uint8_t g;
//         uint8_t green;
//     };
//     union {
//         uint8_t b;
//         uint8_t blue;
//     };
// } rgb_t;

// The actual color is binary with any non-zero value being considered "ON" 
typedef struct
{
    uint8_t red;
    uint8_t green;
    uint8_t blue;
} rgb_t;

extern bool frameBuffer[6][NUM_ROWS * NUM_COLUMNS * 3];

void fillRandom(void);
void setAll(rgb_t color);
void cubeInit(void);
void cubeStart(void);
void cubePause(void);
void setBrightness(float brightness); // 0.0 - 1.0
float getCurrentBrightness(void);
void setPixel(uint8_t panel, uint8_t x, uint8_t y, rgb_t color);
void clearPanel(uint8_t panel);

#ifdef __cplusplus
}
#endif

#endif // __CUBE_H

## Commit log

2023-09-14 [PCB] Split schematic into two board for easier routing
2023-10-04 Update for MTE
2024-10-05 [Firmware] Simple updating firmware complete
2024-10-08 [Effects/Network] Implement Random effect and get barebones http server up and running
2024-10-13 [Networking] Save status before full wifi manager and mDNS incorporation
2024-10-13 [Power] Get battery measurement and basic charger logic implemented
2024-10-15 [Firmware] Basic system loop implemented and working
2025-01-08 [Firmware] MVP complete
2025-03-07 General Sync Before Polish
2025-03-08 Update datasheets and bare minimum README
